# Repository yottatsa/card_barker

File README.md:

# Card Barker OPL3 Sound Card

*WARNING: this project has manufacturability issues: Zilog and two Yamaha chips are virtually unobtainable*

* PCMCIA interface: [Zilog Z86017/Z16017](https://www.zilog.com/index.php?option=com_product&Itemid=26&task=docs&businessLine=&parent_id=139&familyId=13&productId=Z86017)
* OPL3: Yamaha YMF289B-S and YAC516-E
* Amp: [Texas Instruments TPA152DR](http://www.ti.com/lit/gpn/tpa152)

Project status: devboard is working, card hw rev 2 is working, card hw rev 3 goes thru small reDfM. 

## How to run

1. After assembly, upload `fw/vew211.bpd` using `fw/hsc.zip/burner.exe`;
2. Enable using `dos/panas13.lzh/panasnd.exe`, it should start responding on `0x0388-0x038b`;
3. Run `dos/oplclone.zip/oplclone.exe`, it should produce ~460Hz sine.
4. Under Windows 95 and 98, `win9x` contains the proto-driver that only enables the port.

## PCBs

## Related projects

* [FMC-98 reverse engineering](https://github.com/AL-255/A2P1)

## License

Code, designs, and original research: CERN Open Hardware Licence Version 2 - Strongly Reciprocal
Supporting materials: fair use (archived to be protected from bitrot)

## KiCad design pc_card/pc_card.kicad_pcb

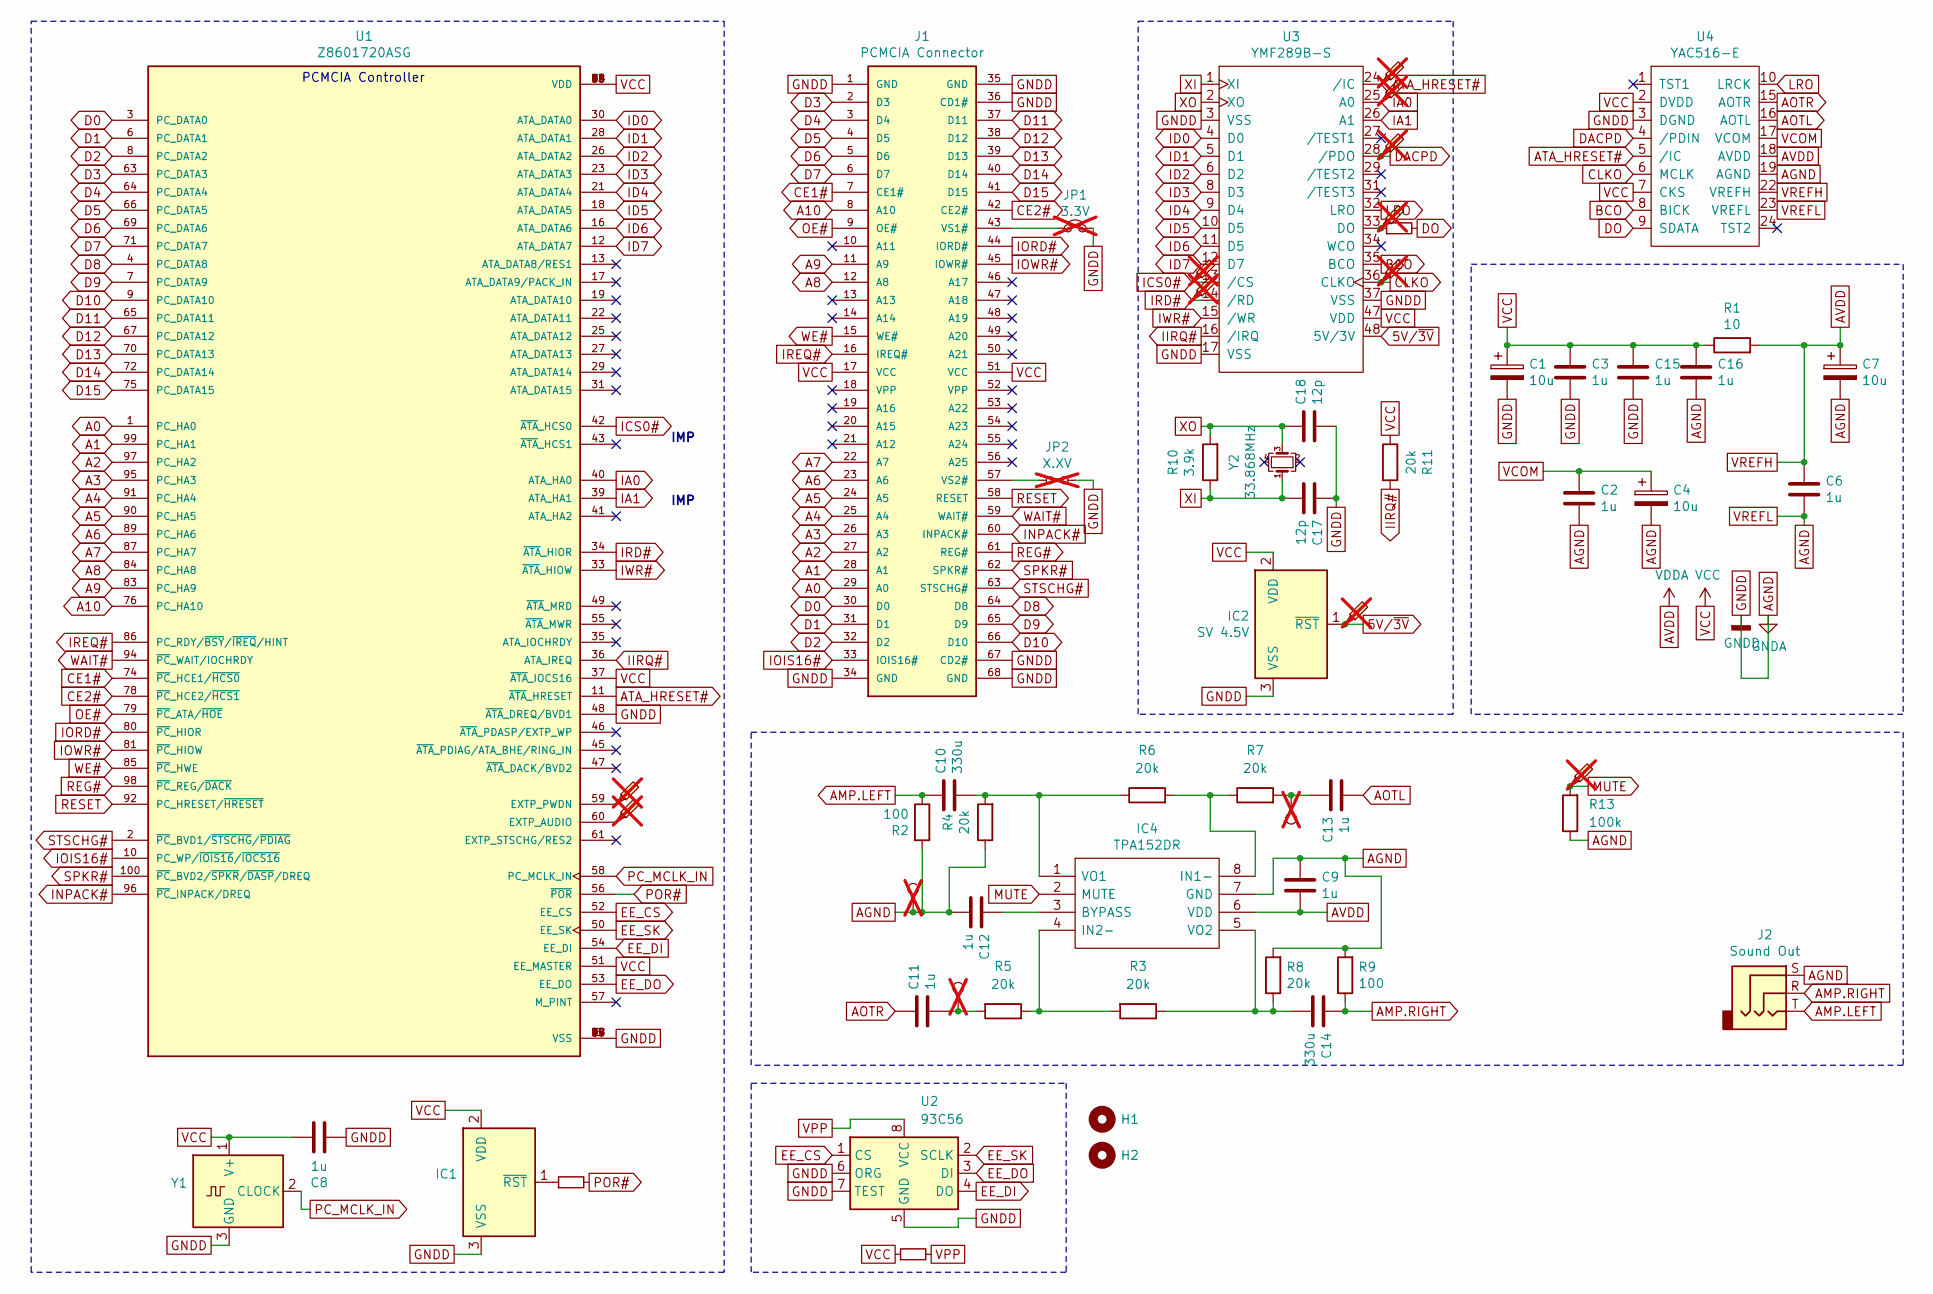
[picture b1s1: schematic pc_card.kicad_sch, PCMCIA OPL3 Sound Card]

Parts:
C1, C4, C7: 10u; CP_EIA-7343-15_Kemet-W_Pad2.25x2.55mm_HandSolder; Manufacturer_Part_Number EEF-CS1D100R; Mouser Part Number 667-EEF-CS1D100R
C2, C3, C6, C8, C15, C16: 1u; C_1206_3216Metric_Pad1.33x1.80mm_HandSolder; Manufacturer_Part_Number C1206X104G4HACTU; Mouser Part Number 80-C1206X104G4HACTU
C9, C11, C12, C13: 1u; C_0805_2012Metric_Pad1.18x1.45mm_HandSolder; Manufacturer_Part_Number C0805C105M3REC7210; Mouser Part Number 80-C0805C105M3RECLR
C10, C14: 330u; C_1210_3225Metric_Pad1.33x2.70mm_HandSolder; Manufacturer_Part_Number GRM32EC80E337ME05L; Mouser Part Number 81-GRM32EC80E337ME5L
C17, C18: 12p; C_0603_1608Metric_Pad1.08x0.95mm_HandSolder; Manufacturer_Part_Number 0603ZA120JAT2A; Mouser Part Number 581-0603ZA120JAT2A
H1, H2: MountingHole
IC1: SV 3.3V; SOT-23; Manufacturer_Part_Number TLV803EB33VDBZR; Mouser Part Number 595-TLV803EB33VDBZR
IC2: SV 4.5V; SOT-23; Manufacturer_Part_Number MCP102T-450E/TT
IC4: TPA152DR; SOIC-8_3.9x4.9mm_P1.27mm; Mouser Part Number 595-TPA152DR
J1: PCMCIA Connector; IC1F-68RD-1.27SF(52); Manufacturer_Part_Number IC1F-68RD-1.27SF(52); Mouser Part Number 798-IC1F68RD127SF52
J2: Sound Out; CUI_SJ1-2533-SMT-TR
JP1: 3.3V; SolderJumper-2_P1.3mm_Bridged_RoundedPad1.0x1.5mm; not fitted
JP2: X.XV; SolderJumper-2_P1.3mm_Open_RoundedPad1.0x1.5mm; not fitted
R1: 10; R_1206_3216Metric_Pad1.30x1.75mm_HandSolder
R2, R9: 100; R_1206_3216Metric_Pad1.30x1.75mm_HandSolder; Manufacturer_Part_Number ERJ-U02F3901X; Mouser Part Number 667-ERJ-U02F3901X
R3, R5, R6, R7: 20k; R_0805_2012Metric_Pad1.20x1.40mm_HandSolder
R4, R8: 20k; R_1206_3216Metric_Pad1.30x1.75mm_HandSolder
R10: 3.9k; R_0603_1608Metric_Pad0.98x0.95mm_HandSolder
R11: 20k; R_0603_1608Metric_Pad0.98x0.95mm_HandSolder
R12: EEPROM; R_0603_1608Metric_Pad0.98x0.95mm_HandSolder
R13: 100k; R_0805_2012Metric_Pad1.20x1.40mm_HandSolder
R14: DO; R_0603_1608Metric_Pad0.98x0.95mm_HandSolder
R15: ~{POR}; R_0603_1608Metric_Pad0.98x0.95mm_HandSolder
TP1: R; TestPoint_Pad_D1.0mm; not fitted
TP2: L; TestPoint_Pad_D1.0mm; not fitted
TP3: ~{CS}; TestPoint_Pad_1.0x1.0mm; not fitted
TP4: GND; TestPoint_Pad_D1.0mm; not fitted
TP5: AMP; TestPoint_Pad_1.0x1.0mm; not fitted
TP6: PWDN; TestPoint_Pad_1.0x1.0mm; not fitted
TP7: AUDIO; TestPoint_Pad_1.0x1.0mm; not fitted
TP8: 5V/~{3V}; TestPoint_Pad_1.0x1.0mm; not fitted
TP9: DO; TestPoint_Pad_1.0x1.0mm; not fitted
TP10: ~{RD}; TestPoint_Pad_1.0x1.0mm; not fitted
TP11: CK; TestPoint_Pad_1.0x1.0mm; not fitted
TP12: ~{PD}; TestPoint_Pad_1.0x1.0mm; not fitted
TP13: A0; TestPoint_Pad_1.0x1.0mm; not fitted
TP14: ~{RESET}; TestPoint_Pad_1.0x1.0mm; not fitted
U1: Z8601720ASG; LQFP-100_14x14mm_P0.5mm; PARTREV Jan, 2005
U2: 93C56; SOIC-8_3.9x4.9mm_P1.27mm; Manufacturer_Part_Number 93C56
U3: YMF289B-S; TQFP-48_7x7mm_P0.5mm; Manufacturer_Part_Number YMF289B-S
U4: YAC516-E; TSSOP-24_6.1x7.8mm_P0.65mm; Manufacturer_Part_Number YAC516-E
Y1: 8MHZ; SOT-323_SC-70; Manufacturer_Part_Number MAX7375AXR805+T; Mouser Part Number 700-MAX7375AXR425T
Y2: 33.868MHz; Crystal_SMD_2520-4Pin_2.5x2.0mm; Manufacturer_Part_Number XRCGB33M868F4M00R0; Mouser Part Number 81-XRCGB33M868F4M0R0

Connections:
5V/~3V: IC2.1 (~RST), TP8.1, U3.48 (5V/3V)
A0: J1.29 (A0), U1.1 (PC_HA0)
A1: J1.28 (A1), U1.99 (PC_HA1)
A2: J1.27 (A2), U1.97 (PC_HA2)
A3: J1.26 (A3), U1.95 (PC_HA3)
A4: J1.25 (A4), U1.91 (PC_HA4)
A5: J1.24 (A5), U1.90 (PC_HA5)
A6: J1.23 (A6), U1.89 (PC_HA6)
A7: J1.22 (A7), U1.87 (PC_HA7)
A8: J1.12 (A8), U1.84 (PC_HA8)
A9: J1.11 (A9), U1.83 (PC_HA9)
A10: J1.8 (A10), U1.76 (PC_HA10)
AGND: C1.2, C2.2, C3.2, C4.2, C6.2, C7.2, C8.1, C9.1, C12.2, C15.2, C16.2, C17.1, C18.2, IC1.3 (VSS), IC2.3 (VSS), IC4.7 (GND), J1.1 (GND), J1.34 (GND), J1.35 (GND), J1.36 (CD1#), J1.67 (CD2#), J1.68 (GND), J2.S, JP1.2, JP2.2, R2.2, R4.1, R8.2, R9.2, R13.1, TP4.1, U1.5 (VSS), U1.15 (VSS), U1.20 (VSS), U1.32 (VSS), U1.44 (VSS), U1.48 (~ATA_DREQ/BVD1), U1.68 (VSS), U1.77 (VSS), U1.88 (VSS), U2.5 (GND), U2.6 (ORG), U2.7 (TEST), U3.3 (VSS), U3.17 (VSS), U3.37 (VSS), U4.3 (DGND), U4.19 (AGND), U4.23 (VREFL), Y1.3 (GND)
AMP.LEFT: C10.1, J2.T, R2.1
AMP.RIGHT: C14.1, J2.R, R9.1
AOTL: C13.2, U4.16 (AOTL)
AOTR: C11.1, U4.15 (AOTR)
ATA_HRESET#: TP14.1, U1.11 (~ATA_HRESET), U3.24 (/IC), U4.5 (/IC)
AVDD: C6.1, C7.1, C9.2, IC4.6 (VDD), R1.2, U4.18 (AVDD), U4.22 (VREFH)
BCO: U3.35 (BCO), U4.8 (BICK)
CE1#: J1.7 (CE1#), U1.74 (~PC_HCE1/~HCS0)
CE2#: J1.42 (CE2#), U1.78 (~PC_HCE2/~HCS1)
CLKO: TP11.1, U3.36 (CLKO), U4.6 (MCLK)
D0: J1.30 (D0), U1.3 (PC_DATA0)
D1: J1.31 (D1), U1.6 (PC_DATA1)
D2: J1.32 (D2), U1.8 (PC_DATA2)
D3: J1.2 (D3), U1.63 (PC_DATA3)
D4: J1.3 (D4), U1.64 (PC_DATA4)
D5: J1.4 (D5), U1.66 (PC_DATA5)
D6: J1.5 (D6), U1.69 (PC_DATA6)
D7: J1.6 (D7), U1.71 (PC_DATA7)
D8: J1.64 (D8), U1.4 (PC_DATA8)
D9: J1.65 (D9), U1.7 (PC_DATA9)
D10: J1.66 (D10), U1.9 (PC_DATA10)
D11: J1.37 (D11), U1.65 (PC_DATA11)
D12: J1.38 (D12), U1.67 (PC_DATA12)
D13: J1.39 (D13), U1.70 (PC_DATA13)
D14: J1.40 (D14), U1.72 (PC_DATA14)
D15: J1.41 (D15), U1.75 (PC_DATA15)
DACPD: TP12.1, U3.28 (/PDO), U4.4 (/PDIN)
DO: R14.2, U4.9 (SDATA)
EE_CS: U1.52 (EE_CS), U2.1 (CS)
EE_DI: U1.54 (EE_DI), U2.4 (DO)
EE_DO: U1.53 (EE_DO), U2.3 (DI)
EE_SK: U1.50 (EE_SK), U2.2 (SCLK)
IA0: TP13.1, U1.40 (ATA_HA0), U3.25 (A0)
IA1: U1.39 (ATA_HA1), U3.26 (A1)
ICS0#: TP3.1, U1.42 (~ATA_HCS0), U3.13 (/CS)
ID0: U1.30 (ATA_DATA0), U3.4 (D0)
ID1: U1.28 (ATA_DATA1), U3.5 (D1)
ID2: U1.26 (ATA_DATA2), U3.6 (D2)
ID3: U1.23 (ATA_DATA3), U3.8 (D3)
ID4: U1.21 (ATA_DATA4), U3.9 (D4)
ID5: U1.18 (ATA_DATA5), U3.10 (D5)
ID6: U1.16 (ATA_DATA6), U3.11 (D5)
ID7: U1.12 (ATA_DATA7), U3.12 (D7)
IIRQ#: R11.2, U1.36 (ATA_IREQ), U3.16 (/IRQ)
INPACK#: J1.60 (INPACK#), U1.96 (~PC_INPACK/DREQ)
IOIS16#: J1.33 (IOIS16#), U1.10 (PC_WP/~IOIS16/~IOCS16)
IORD#: J1.44 (IORD#), U1.80 (~PC_HIOR)
IOWR#: J1.45 (IOWR#), U1.81 (~PC_HIOW)
IRD#: TP10.1, U1.34 (~ATA_HIOR), U3.14 (/RD)
IREQ#: J1.16 (IREQ#), U1.86 (PC_RDY/~BSY/~IREQ/HINT)
IWR#: U1.33 (~ATA_HIOW), U3.15 (/WR)
LRO: U3.32 (LRO), U4.10 (LRCK)
MUTE: IC4.2 (MUTE), R13.2, TP5.1
unnamed: C11.2, R5.2, TP1.1
unnamed: C13.1, R7.2, TP2.1
unnamed: IC1.1 (~RST), R15.1
unnamed: C12.1, IC4.3 (BYPASS)
unnamed: IC4.8 (IN1-), R6.2, R7.1
unnamed: IC4.4 (IN2-), R3.2, R5.1
unnamed: C10.2, IC4.1 (VO1), R4.2, R6.1
unnamed: C14.2, IC4.5 (VO2), R3.1, R8.1
unnamed: J1.43 (VS1#), JP1.1
unnamed: J1.57 (VS2#), JP2.1
unnamed: TP7.1, U1.60 (EXTP_AUDIO)
unnamed: TP6.1, U1.59 (EXTP_PWDN)
unnamed: R14.1, TP9.1, U3.33 (DO)
OE#: J1.9 (OE#), U1.79 (~PC_ATA/~HOE)
PC_MCLK_IN: U1.58 (PC_MCLK_IN), Y1.2 (CLOCK)
POR#: R15.2, U1.56 (~POR)
REG#: J1.61 (REG#), U1.98 (~PC_REG/~DACK)
RESET: J1.58 (RESET), U1.92 (PC_HRESET/~HRESET)
SPKR#: J1.62 (SPKR#), U1.100 (~PC_BVD2/~SPKR/~DASP/DREQ)
STSCHG#: J1.63 (STSCHG#), U1.2 (~PC_BVD1/~STSCHG/~PDIAG)
VCC: C1.1, C3.1, C8.2, C15.1, C16.1, IC1.2 (VDD), IC2.2 (VDD), J1.17 (VCC), J1.51 (VCC), R1.1, R11.1, R12.1, U1.14 (VDD), U1.24 (VDD), U1.37 (~ATA_IOCS16), U1.38 (VDD), U1.51 (EE_MASTER), U1.62 (VDD), U1.73 (VDD), U1.82 (VDD), U1.93 (VDD), U3.47 (VDD), U4.2 (DVDD), U4.7 (CKS), Y1.1 (V+)
VCOM: C2.1, C4.1, U4.17 (VCOM)
VPP: R12.2, U2.8 (VCC)
WAIT#: J1.59 (WAIT#), U1.94 (~PC_WAIT/IOCHRDY)
WE#: J1.15 (WE#), U1.85 (~PC_HWE)
XI: C17.2, R10.1, U3.1 (XI), Y2.1
XO: C18.1, R10.2, U3.2 (XO), Y2.3

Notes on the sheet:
IMP
PCMCIA Controller

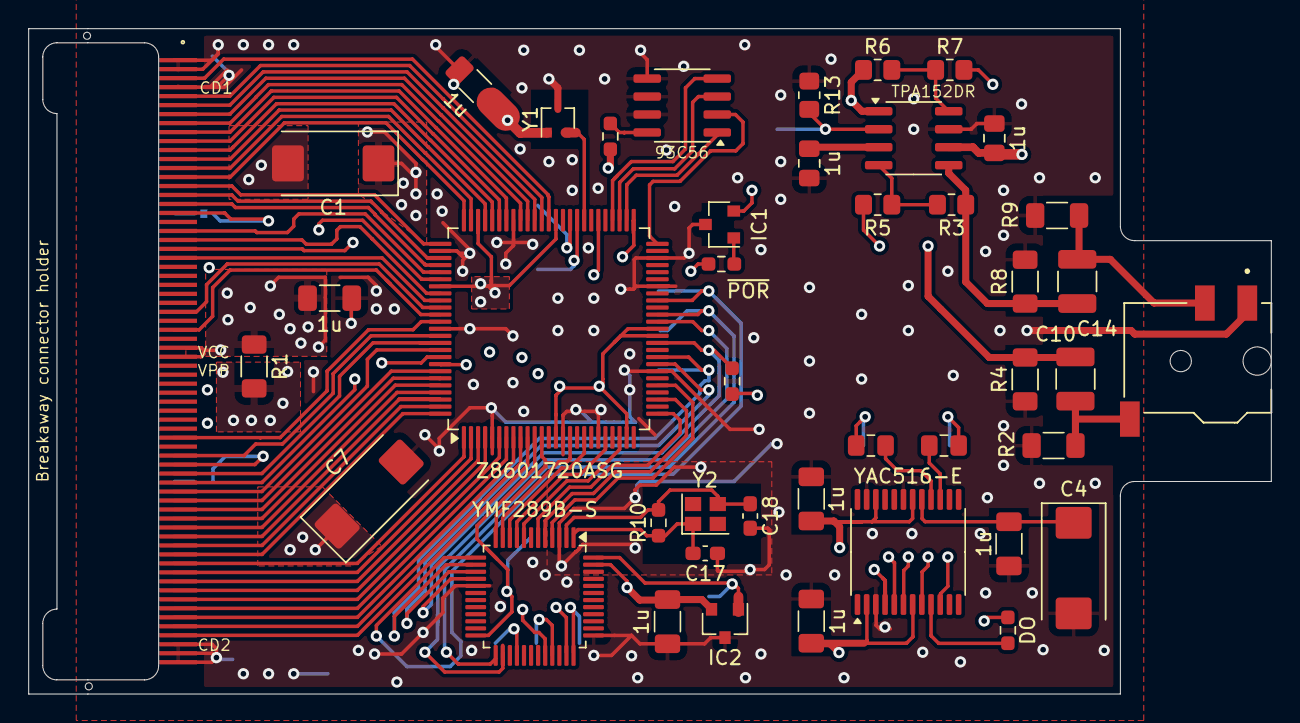
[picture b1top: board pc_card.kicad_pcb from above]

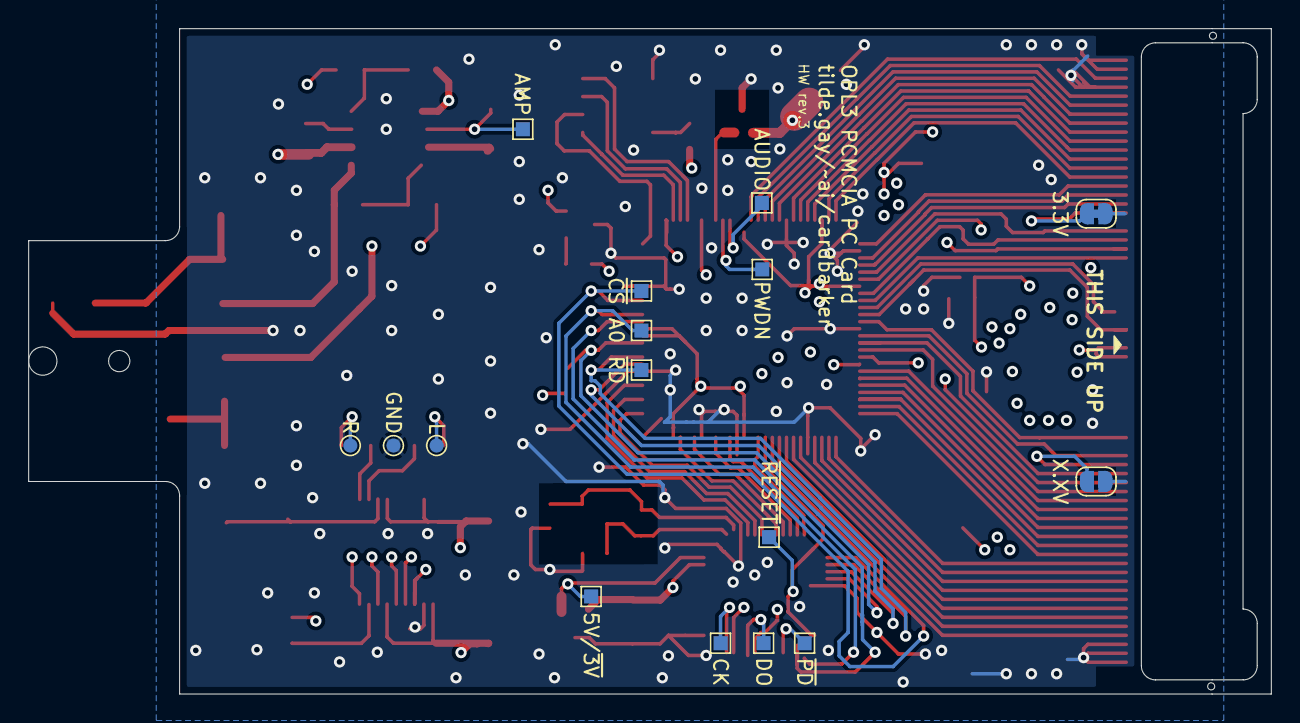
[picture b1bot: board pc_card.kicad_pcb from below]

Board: 4 copper layers, 87.8 x 47.0 mm, 61 parts (16 on the bottom side), 93 nets.

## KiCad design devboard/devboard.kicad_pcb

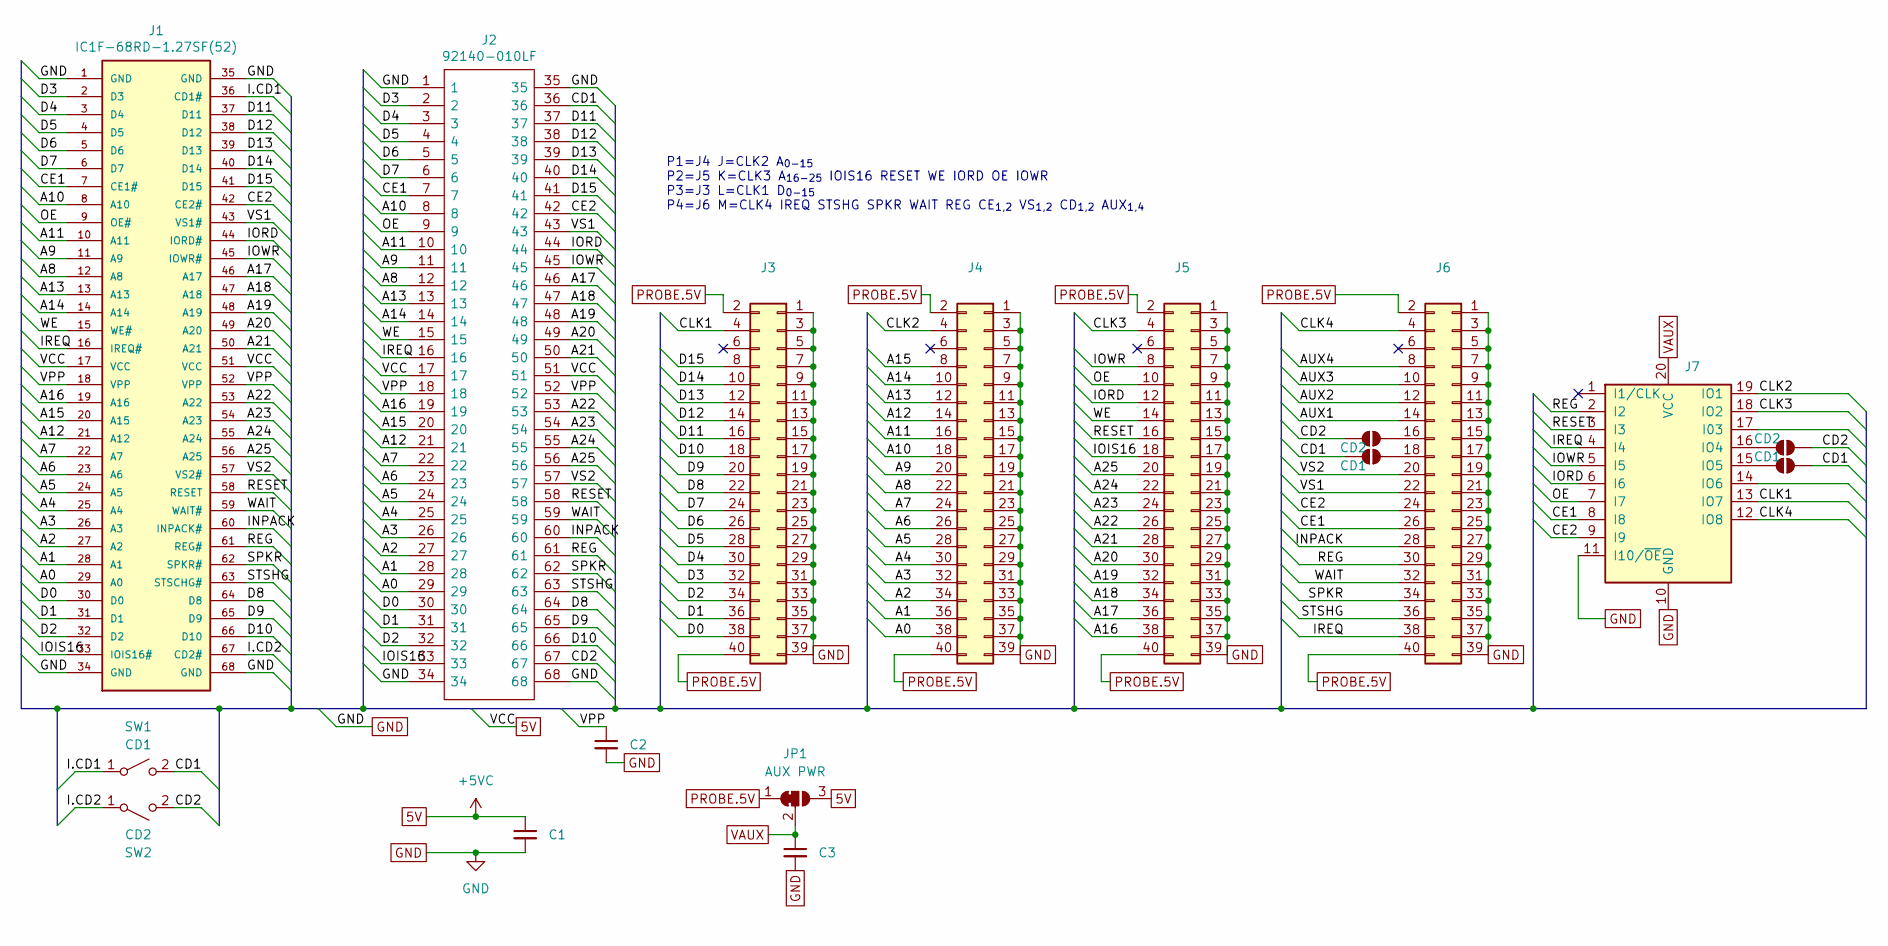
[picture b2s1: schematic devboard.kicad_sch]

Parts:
C1, C2, C3: 1uF PWR; C_1206_3216Metric_Pad1.33x1.80mm_HandSolder; Mouser Part Number 80-C1206X104G4HACTU
J1: IC1F-68RD-1.27SF(52); 95622003LF
J2: 92140-010LF; 92140010LF; Mouser Part Number 649-92140-010LF
J3: D_{0-15}; Hirose_FH12-40S-0.5SH_1x40-1MP_P0.50mm_Horizontal
J4: A_{0-15}; Hirose_FH12-40S-0.5SH_1x40-1MP_P0.50mm_Horizontal
J5: A_{16-25} IOIS16 RESET WE IORD OE IOWR; Hirose_FH12-40S-0.5SH_1x40-1MP_P0.50mm_Horizontal
J6: IREQ STSHG SPKR WAIT REG CE_{1,2} VS_{1,2} CD_{1,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; Hirose_FH12-40S-0.5SH_1x40-1MP_P0.50mm_Horizontal
J7: REG RESET IREQ IOWR IORD OE CE_{1,2}; DIP-20_W7.62mm
JP1: AUX PWR; SolderJumper-3_P1.3mm_Bridged12_Pad1.0x1.5mm
JP2, JP5: CD2; SolderJumper-2_P1.3mm_Open_RoundedPad1.0x1.5mm
JP3, JP4: CD1; SolderJumper-2_P1.3mm_Open_RoundedPad1.0x1.5mm
SW1: CD1; D_DO-15_P3.81mm_Vertical_AnodeUp
SW2: CD2; D_DO-15_P3.81mm_Vertical_AnodeUp

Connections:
5V: C1.1, J1.17 (VCC), J1.51 (VCC), J2.17, J2.51, JP1.3 (B)
/A0: J1.29 (A0), J2.29, J4.38
/A1: J1.28 (A1), J2.28, J4.36
/A2: J1.27 (A2), J2.27, J4.34
/A3: J1.26 (A3), J2.26, J4.32
/A4: J1.25 (A4), J2.25, J4.30
/A5: J1.24 (A5), J2.24, J4.28
/A6: J1.23 (A6), J2.23, J4.26
/A7: J1.22 (A7), J2.22, J4.24
/A8: J1.12 (A8), J2.12, J4.22
/A9: J1.11 (A9), J2.11, J4.20
/A10: J1.8 (A10), J2.8, J4.18
/A11: J1.10 (A11), J2.10, J4.16
/A12: J1.21 (A12), J2.21, J4.14
/A13: J1.13 (A13), J2.13, J4.12
/A14: J1.14 (A14), J2.14, J4.10
/A15: J1.20 (A15), J2.20, J4.8
/A16: J1.19 (A16), J2.19, J5.38
/A17: J1.46 (A17), J2.46, J5.36
/A18: J1.47 (A18), J2.47, J5.34
/A19: J1.48 (A19), J2.48, J5.32
/A20: J1.49 (A20), J2.49, J5.30
/A21: J1.50 (A21), J2.50, J5.28
/A22: J1.53 (A22), J2.53, J5.26
/A23: J1.54 (A23), J2.54, J5.24
/A24: J1.55 (A24), J2.55, J5.22
/A25: J1.56 (A25), J2.56, J5.20
/AUX1: J6.14
/AUX2: J6.12
/AUX3: J6.10
/AUX4: J6.8
/CD1: J2.36, JP3.2 (B), JP4.1 (A), SW1.2 (B)
/CD2: J2.67, JP2.2 (B), JP5.1 (A), SW2.2 (B)
/CE1: J1.7 (CE1#), J2.7, J6.26, J7.8 (I8)
/CE2: J1.42 (CE2#), J2.42, J6.24, J7.9 (I9)
/CLK1: J3.4, J7.13 (IO7)
/CLK2: J4.4, J7.19 (IO1)
/CLK3: J5.4, J7.18 (IO2)
/CLK4: J6.4, J7.12 (IO8)
/D0: J1.30 (D0), J2.30, J3.38
/D1: J1.31 (D1), J2.31, J3.36
/D2: J1.32 (D2), J2.32, J3.34
/D3: J1.2 (D3), J2.2, J3.32
/D4: J1.3 (D4), J2.3, J3.30
/D5: J1.4 (D5), J2.4, J3.28
/D6: J1.5 (D6), J2.5, J3.26
/D7: J1.6 (D7), J2.6, J3.24
/D8: J1.64 (D8), J2.64, J3.22
/D9: J1.65 (D9), J2.65, J3.20
/D10: J1.66 (D10), J2.66, J3.18
/D11: J1.37 (D11), J2.37, J3.16
/D12: J1.38 (D12), J2.38, J3.14
/D13: J1.39 (D13), J2.39, J3.12
/D14: J1.40 (D14), J2.40, J3.10
/D15: J1.41 (D15), J2.41, J3.8
/I.CD1: J1.36 (CD1#), SW1.1 (A)
/I.CD2: J1.67 (CD2#), SW2.1 (A)
/INPACK: J1.60 (INPACK#), J2.60, J6.28
/IOIS16: J1.33 (IOIS16#), J2.33, J5.18
/IORD: J1.44 (IORD#), J2.44, J5.12, J7.6 (I6)
/IOWR: J1.45 (IOWR#), J2.45, J5.8, J7.5 (I5)
/IREQ: J1.16 (IREQ#), J2.16, J6.38, J7.4 (I4)
/OE: J1.9 (OE#), J2.9, J5.10, J7.7 (I7)
/REG: J1.61 (REG#), J2.61, J6.30, J7.2 (I2)
/RESET: J1.58 (RESET), J2.58, J5.16, J7.3 (I3)
/SPKR: J1.62 (SPKR#), J2.62, J6.34
/STSHG: J1.63 (STSCHG#), J2.63, J6.36
/VPP: C2.1, J1.18 (VPP), J1.52 (VPP), J2.18, J2.52
/VS1: J1.43 (VS1#), J2.43, J6.22
/VS2: J1.57 (VS2#), J2.57, J6.20
/WAIT: J1.59 (WAIT#), J2.59, J6.32
/WE: J1.15 (WE#), J2.15, J5.14
GND: C1.2, C2.2, C3.2, J1.1 (GND), J1.34 (GND), J1.35 (GND), J1.68 (GND), J2.1, J2.34, J2.35, J2.68, J3.1, J3.3, J3.5, J3.7, J3.9, J3.11, J3.13, J3.15, J3.17, J3.19, J3.21, J3.23, J3.25, J3.27, J3.29, J3.31, J3.33, J3.35, J3.37, J3.39, J4.1, J4.3, J4.5, J4.7, J4.9, J4.11, J4.13, J4.15, J4.17, J4.19, J4.21, J4.23, J4.25, J4.27, J4.29, J4.31, J4.33, J4.35, J4.37, J4.39, J5.1, J5.3, J5.5, J5.7, J5.9, J5.11, J5.13, J5.15, J5.17, J5.19, J5.21, J5.23, J5.25, J5.27, J5.29, J5.31, J5.33, J5.35, J5.37, J5.39, J6.1, J6.3, J6.5, J6.7, J6.9, J6.11, J6.13, J6.15, J6.17, J6.19, J6.21, J6.23, J6.25, J6.27, J6.29, J6.31, J6.33, J6.35, J6.37, J6.39, J7.10 (GND), J7.11 (I10/~OE)
unnamed: J6.16, JP5.2 (B)
unnamed: J6.18, JP4.2 (B)
unnamed: J7.16 (IO4), JP2.1 (A)
unnamed: J7.15 (IO5), JP3.1 (A)
PROBE.5V: J3.2, J3.40, J4.2, J4.40, J5.2, J5.40, J6.2, J6.40, JP1.1 (A)
VAUX: C3.1, J7.20 (VCC), JP1.2 (C)

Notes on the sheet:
P1=J4 J=CLK2 A_{0-15} P2=J5 K=CLK3 A_{16-25} IOIS16 RESET WE IORD OE IOWR P3=J3 L=CLK1 D_{0-15} P4=J6 M=CLK4 IREQ STSHG SPKR WAIT REG CE_{1,2} VS_{1,2} CD_{1,2} AUX_{1,4}

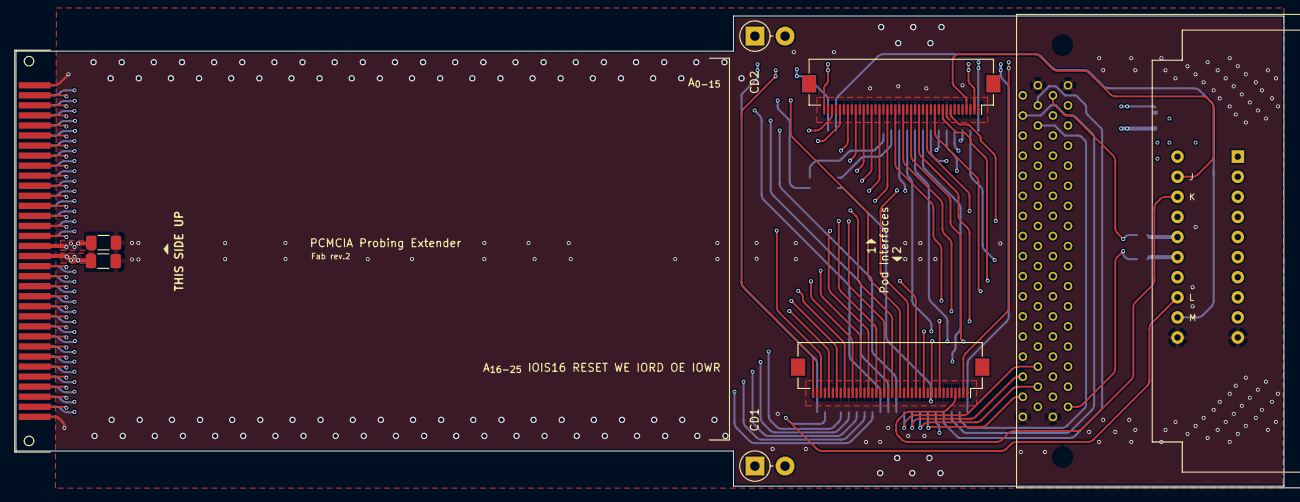
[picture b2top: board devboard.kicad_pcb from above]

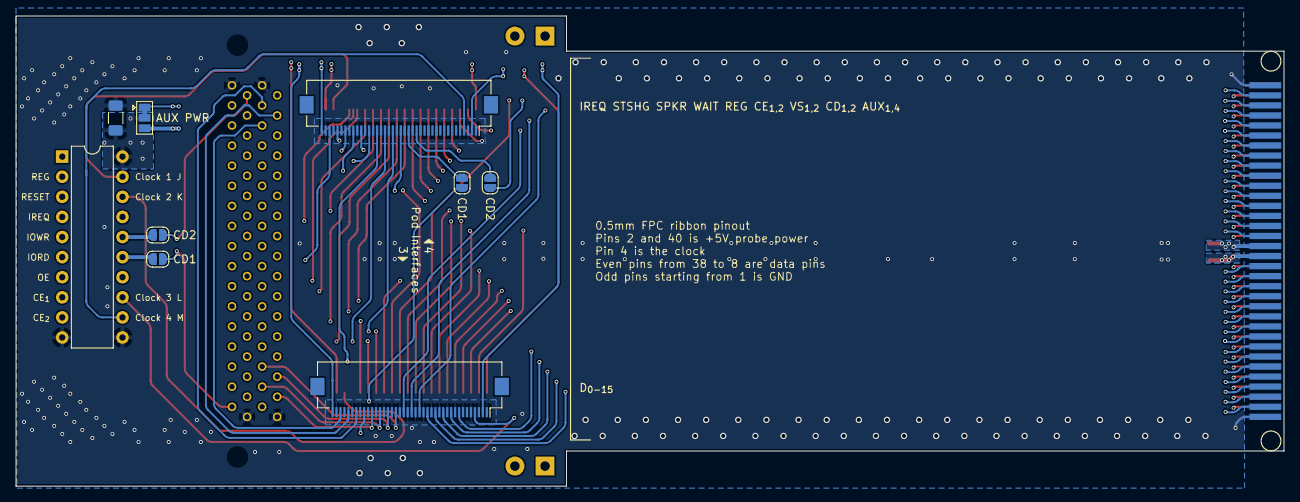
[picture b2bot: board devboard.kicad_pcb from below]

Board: 4 copper layers, 160.3 x 59.4 mm, 17 parts (9 on the bottom side), 75 nets.

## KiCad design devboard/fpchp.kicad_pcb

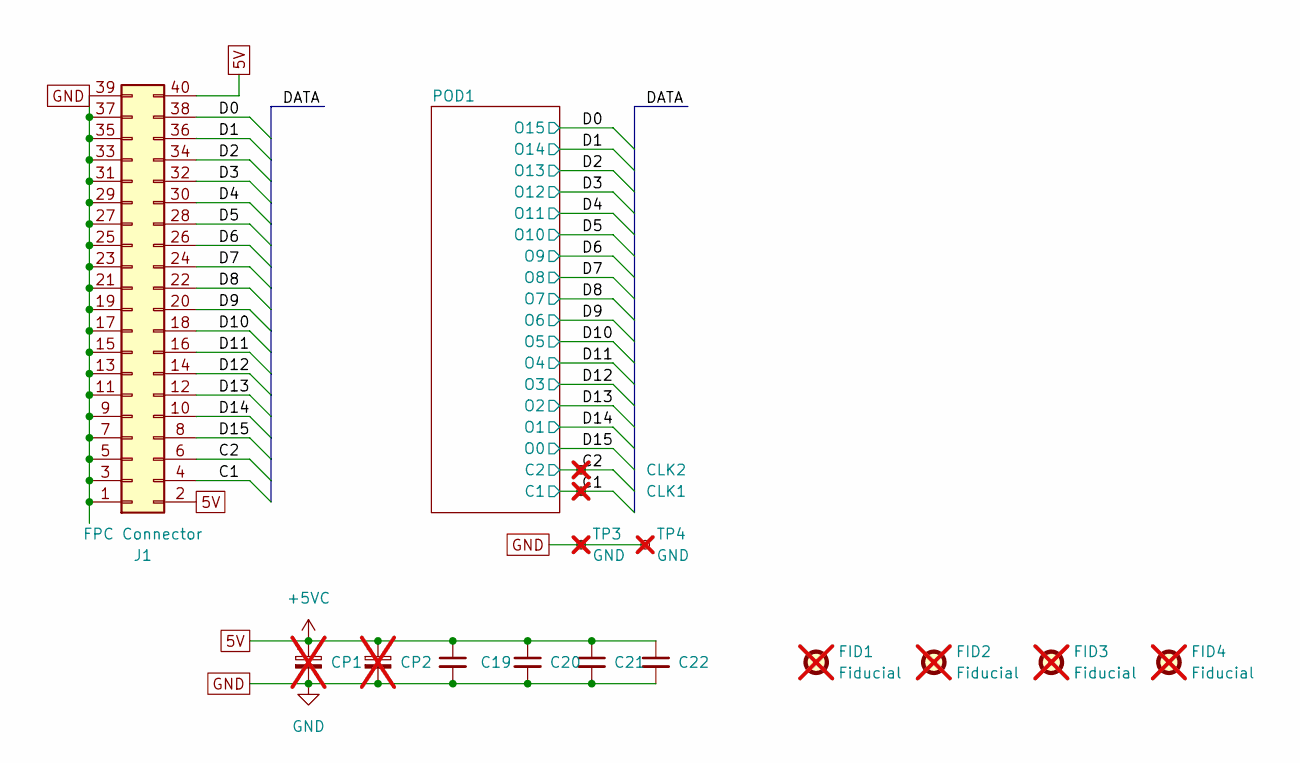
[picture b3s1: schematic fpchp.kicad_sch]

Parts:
C19, C20, C21, C22: 1uF PWR; C_1206_3216Metric_Pad1.33x1.80mm_HandSolder; Mouser Part Number 80-C1206X104G4HACTU
CP1, CP2: PPWR; CP_EIA-7343-31_Kemet-D; Mouser Part Number 667-EEF-CS1D100R; not fitted
FID1, FID2, FID3, FID4: Fiducial; not fitted
J1: FPC Connector; Hirose_FH12-40S-0.5SH_1x40-1MP_P0.50mm_Horizontal
TP1: CLK2; TestPoint_THTPad_1.0x1.0mm_Drill0.5mm; not fitted
TP2: CLK1; TestPoint_THTPad_1.0x1.0mm_Drill0.5mm; not fitted
TP3, TP4: GND; TestPoint_THTPad_1.0x1.0mm_Drill0.5mm; not fitted

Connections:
5V: C19.1, C20.1, C21.1, C22.1, CP1.1, CP2.1, J1.2, J1.40; also elsewhere on the board
/C1: J1.4, TP2.1; also elsewhere on the board
/C2: J1.6, TP1.1; also elsewhere on the board
/D0: J1.38; also elsewhere on the board
/D1: J1.36; also elsewhere on the board
/D2: J1.34; also elsewhere on the board
/D3: J1.32; also elsewhere on the board
/D4: J1.30; also elsewhere on the board
/D5: J1.28; also elsewhere on the board
/D6: J1.26; also elsewhere on the board
/D7: J1.24; also elsewhere on the board
/D8: J1.22; also elsewhere on the board
/D9: J1.20; also elsewhere on the board
/D10: J1.18; also elsewhere on the board
/D11: J1.16; also elsewhere on the board
/D12: J1.14; also elsewhere on the board
/D13: J1.12; also elsewhere on the board
/D14: J1.10; also elsewhere on the board
/D15: J1.8; also elsewhere on the board
GND: C19.2, C20.2, C21.2, C22.2, CP1.2, CP2.2, J1.1, J1.3, J1.5, J1.7, J1.9, J1.11, J1.13, J1.15, J1.17, J1.19, J1.21, J1.23, J1.25, J1.27, J1.29, J1.31, J1.33, J1.35, J1.37, J1.39, TP3.1, TP4.1; also elsewhere on the board

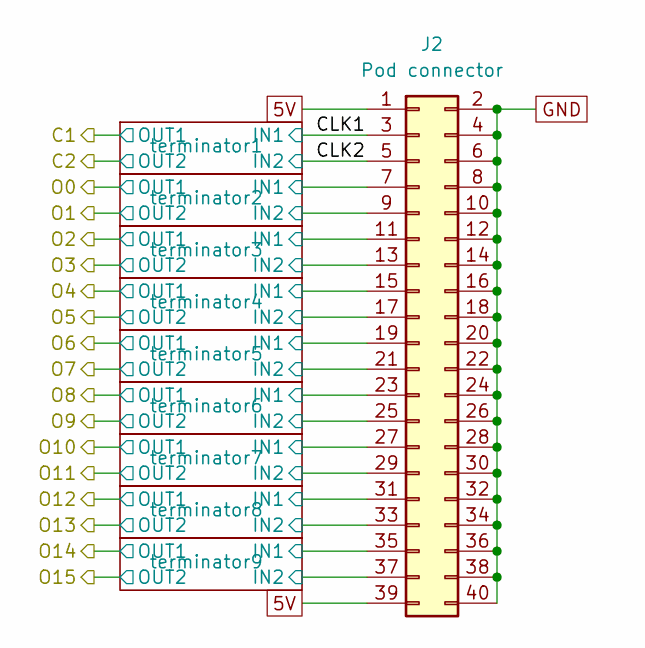
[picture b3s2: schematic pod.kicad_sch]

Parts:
J2: Pod connector; IDC-Header_2x20_P2.54mm_Vertical

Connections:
5V: J2.1, J2.39; also elsewhere on the board
/POD1/CLK1: J2.3; also elsewhere on the board
/POD1/CLK2: J2.5; also elsewhere on the board
/POD1/terminator2/IN1: J2.7; also elsewhere on the board
/POD1/terminator2/IN2: J2.9; also elsewhere on the board
/POD1/terminator3/IN1: J2.11; also elsewhere on the board
/POD1/terminator3/IN2: J2.13; also elsewhere on the board
/POD1/terminator4/IN1: J2.15; also elsewhere on the board
/POD1/terminator4/IN2: J2.17; also elsewhere on the board
/POD1/terminator5/IN1: J2.19; also elsewhere on the board
/POD1/terminator5/IN2: J2.21; also elsewhere on the board
/POD1/terminator6/IN1: J2.23; also elsewhere on the board
/POD1/terminator6/IN2: J2.25; also elsewhere on the board
/POD1/terminator7/IN1: J2.27; also elsewhere on the board
/POD1/terminator7/IN2: J2.29; also elsewhere on the board
/POD1/terminator8/IN1: J2.31; also elsewhere on the board
/POD1/terminator8/IN2: J2.33; also elsewhere on the board
/POD1/terminator9/IN1: J2.35; also elsewhere on the board
/POD1/terminator9/IN2: J2.37; also elsewhere on the board
GND: J2.2, J2.4, J2.6, J2.8, J2.10, J2.12, J2.14, J2.16, J2.18, J2.20, J2.22, J2.24, J2.26, J2.28, J2.30, J2.32, J2.34, J2.36, J2.38, J2.40; also elsewhere on the board

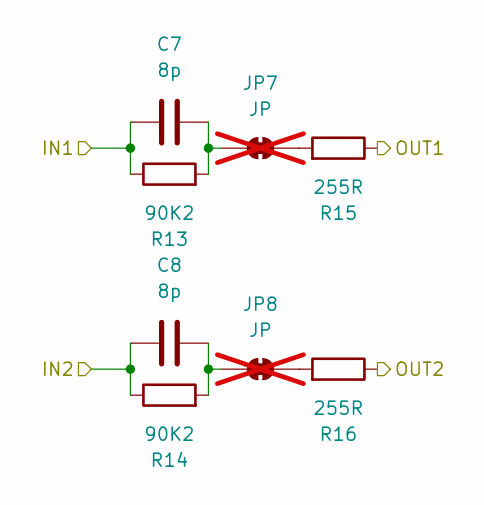
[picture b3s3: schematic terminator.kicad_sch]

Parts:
C7, C8: 8p; C_0402_1005Metric
JP7, JP8: JP; SolderJumper-2_P1.3mm_Bridged_RoundedPad1.0x1.5mm; not fitted
R13, R14: 90K2; R_0402_1005Metric
R15, R16: 255R; R_0402_1005Metric

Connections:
/D10: R16.1; also elsewhere on the board
/D11: R15.1; also elsewhere on the board
/POD1/terminator4/IN1: C7.2, R13.1; also elsewhere on the board
/POD1/terminator4/IN2: C8.2, R14.1; also elsewhere on the board
unnamed: JP7.1 (A), R15.2
unnamed: C7.1, JP7.2 (B), R13.2
unnamed: JP8.1 (A), R16.2
unnamed: C8.1, JP8.2 (B), R14.2

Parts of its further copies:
C1, C2, C3, C4, C5, C6, C9, C10, C11, C12, C13, C14, C15, C16, C17, C18: 8p; C_0402_1005Metric
JP1, JP2, JP3, JP4, JP5, JP6, JP9, JP10, JP11, JP12, JP13, JP14, JP15, JP16, JP17, JP18: JP; SolderJumper-2_P1.3mm_Bridged_RoundedPad1.0x1.5mm; not fitted
R1, R2, R5, R6, R9, R10, R17, R18, R21, R22, R25, R26, R29, R30, R33, R34: 90K2; R_0402_1005Metric
R3, R4, R7, R8, R11, R12, R19, R20, R23, R24, R27, R28, R31, R32, R35, R36: 255R; R_0402_1005Metric

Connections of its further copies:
/C1: R3.1; also elsewhere on the board
/C2: R4.1; also elsewhere on the board
/D0: R36.1; also elsewhere on the board
/D1: R35.1; also elsewhere on the board
/D2: R32.1; also elsewhere on the board
/D3: R31.1; also elsewhere on the board
/D4: R28.1; also elsewhere on the board
/D5: R27.1; also elsewhere on the board
/D6: R24.1; also elsewhere on the board
/D7: R23.1; also elsewhere on the board
/D8: R20.1; also elsewhere on the board
/D9: R19.1; also elsewhere on the board
/D12: R12.1; also elsewhere on the board
/D13: R11.1; also elsewhere on the board
/D14: R8.1; also elsewhere on the board
/D15: R7.1; also elsewhere on the board
/POD1/CLK1: C1.2, R1.1; also elsewhere on the board
/POD1/CLK2: C2.2, R2.1; also elsewhere on the board
/POD1/terminator2/IN1: C3.2, R5.1; also elsewhere on the board
/POD1/terminator2/IN2: C4.2, R6.1; also elsewhere on the board
/POD1/terminator3/IN1: C5.2, R9.1; also elsewhere on the board
/POD1/terminator3/IN2: C6.2, R10.1; also elsewhere on the board
/POD1/terminator5/IN1: C9.2, R17.1; also elsewhere on the board
/POD1/terminator5/IN2: C10.2, R18.1; also elsewhere on the board
/POD1/terminator6/IN1: C11.2, R21.1; also elsewhere on the board
/POD1/terminator6/IN2: C12.2, R22.1; also elsewhere on the board
/POD1/terminator7/IN1: C13.2, R25.1; also elsewhere on the board
/POD1/terminator7/IN2: C14.2, R26.1; also elsewhere on the board
/POD1/terminator8/IN1: C15.2, R29.1; also elsewhere on the board
/POD1/terminator8/IN2: C16.2, R30.1; also elsewhere on the board
/POD1/terminator9/IN1: C17.2, R33.1; also elsewhere on the board
/POD1/terminator9/IN2: C18.2, R34.1; also elsewhere on the board
unnamed: JP1.1 (A), R3.2
unnamed: C1.1, JP1.2 (B), R1.2
unnamed: JP2.1 (A), R4.2
unnamed: C2.1, JP2.2 (B), R2.2
unnamed: JP3.1 (A), R7.2
unnamed: C3.1, JP3.2 (B), R5.2
unnamed: JP4.1 (A), R8.2
unnamed: C4.1, JP4.2 (B), R6.2
unnamed: JP5.1 (A), R11.2
unnamed: C5.1, JP5.2 (B), R9.2
unnamed: JP6.1 (A), R12.2
unnamed: C6.1, JP6.2 (B), R10.2
unnamed: JP9.1 (A), R19.2
unnamed: C9.1, JP9.2 (B), R17.2
unnamed: JP10.1 (A), R20.2
unnamed: C10.1, JP10.2 (B), R18.2
unnamed: JP11.1 (A), R23.2
unnamed: C11.1, JP11.2 (B), R21.2
unnamed: JP12.1 (A), R24.2
unnamed: C12.1, JP12.2 (B), R22.2
unnamed: JP13.1 (A), R27.2
unnamed: C13.1, JP13.2 (B), R25.2
unnamed: JP14.1 (A), R28.2
unnamed: C14.1, JP14.2 (B), R26.2
unnamed: JP15.1 (A), R31.2
unnamed: C15.1, JP15.2 (B), R29.2
unnamed: JP16.1 (A), R32.2
unnamed: C16.1, JP16.2 (B), R30.2
unnamed: JP17.1 (A), R35.2
unnamed: C17.1, JP17.2 (B), R33.2
unnamed: JP18.1 (A), R36.2
unnamed: C18.1, JP18.2 (B), R34.2

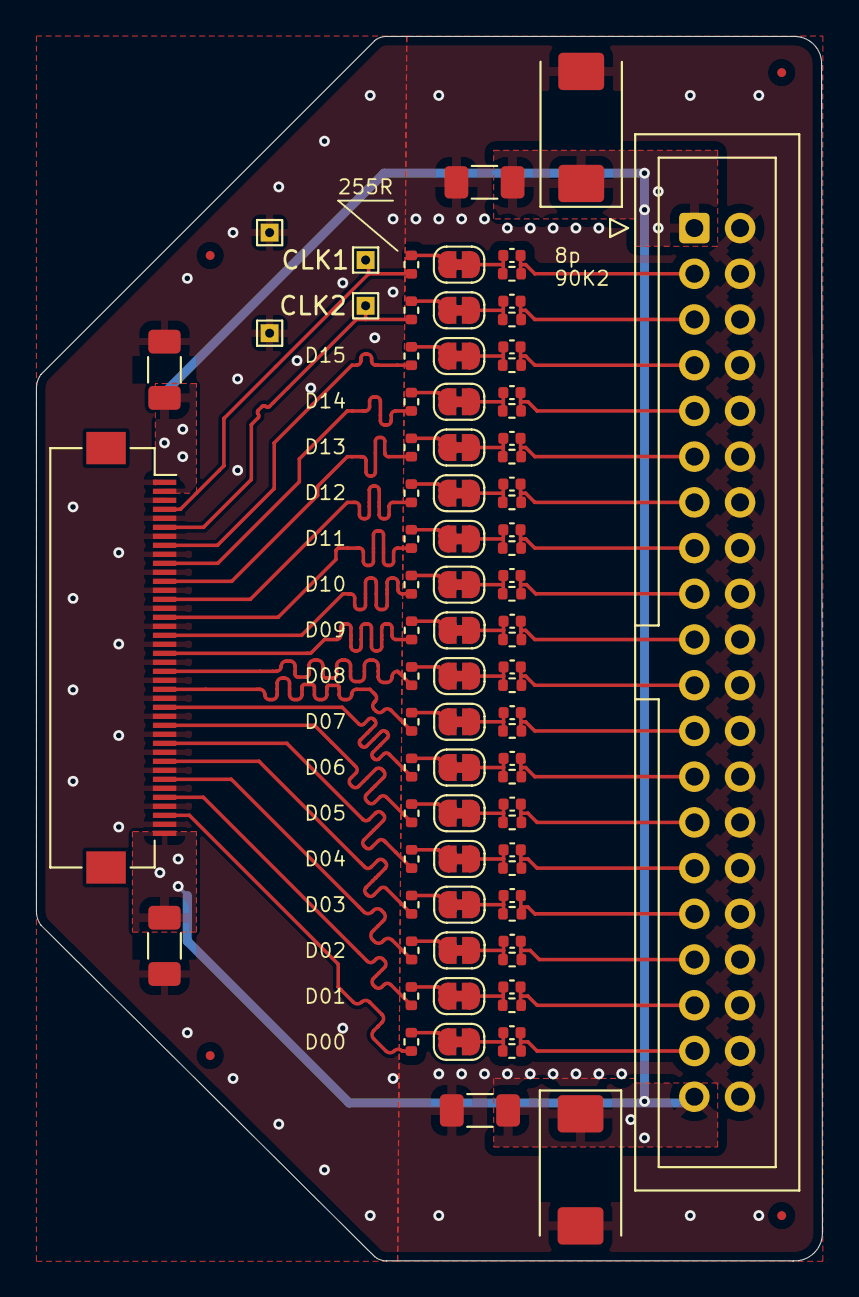
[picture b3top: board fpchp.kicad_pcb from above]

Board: 2 copper layers, 43.7 x 68.0 mm, 88 parts (0 on the bottom side), 74 nets.

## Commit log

2021-11-29 BOM, tracks, cleanup
2021-11-29 remove pull-downs for unused address lines
2021-11-29 firmware configurator
2021-11-30 eeprom is isolated for onboard programming
2021-12-04 full eeprom
2021-12-05 devboard prototype
2021-12-05 README
2021-12-23 CIS generation: more tuples
2021-12-23 CIS generation: CISTPL_CONFIG but with no TPCC_SZ
2021-12-23 CIS generation: CISTPL_CFTABLE_ENTRY as raw
2024-08-06 new devboard
    Adding 4 x 40 lines 0.5mm FPC ribbon connectors, 16 probing lines each.
2024-08-06 fixes
2024-08-09 devboard; finishing 4L card
2024-08-09 dut illustration
2024-08-12 render, stl
2024-08-31 devboard to hp16xx adapter fab.rev 2
2024-08-31 ground reshuffle
2024-09-06 hp adapter rev.2
2024-09-08 card hw rev 2 to manufacture
2024-09-08 docs, stl
2024-09-20 pld, docs
2024-09-20 devboard test
2025-01-21 FMC-98 regs and cis
2025-01-21 decoded FMC-98 flags
2025-01-21 patched for python3.9 with poor girls namedtuple metaclass
2025-01-21 almost decoded card info
2025-01-22 fully decoded card info
2025-01-22 pulling the io port
2025-01-23 decoded txt
2025-01-27 another FW
2025-01-28 cis decoded using pcmcia_cs
2025-01-29 HeadstartCard initial fw and utilities
2025-01-29 original hsc
2025-01-31 fw readme
2025-02-02 better clock
2025-02-03 Panasonic CF-VEW211
2025-02-03 working configs
2025-02-03 hp166c config and screenshots
2025-02-03 timings
2025-02-04 correct decoding
2025-02-06 hw rev3
    * reDfMing the card so the connector can be assembled easier
    * added software and specs
2025-02-06 fiddling with connector
2025-02-07 socket assembly
2025-02-07 messing with xtal
2025-07-01 INF file
2025-07-01 win9x readme
2025-07-03 small rename
2025-07-03 even more minimalist driver, fw generation works for windows
2025-07-03 docs
2025-07-04 license
2025-07-05 disassembled ena86r
2025-07-06 ..it was pc98 registers
2025-07-06 pcmcia chip registers list
